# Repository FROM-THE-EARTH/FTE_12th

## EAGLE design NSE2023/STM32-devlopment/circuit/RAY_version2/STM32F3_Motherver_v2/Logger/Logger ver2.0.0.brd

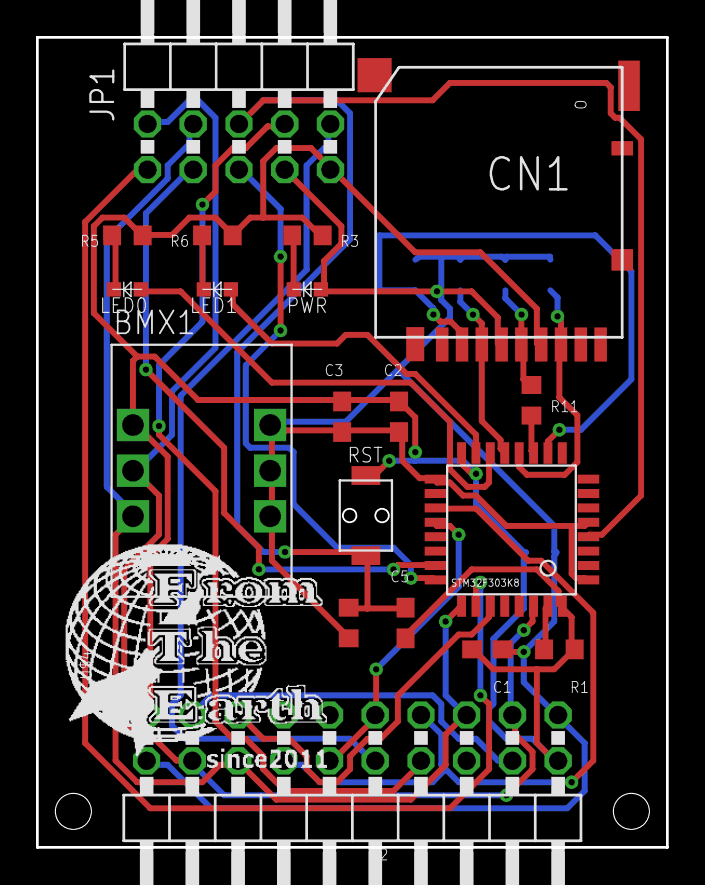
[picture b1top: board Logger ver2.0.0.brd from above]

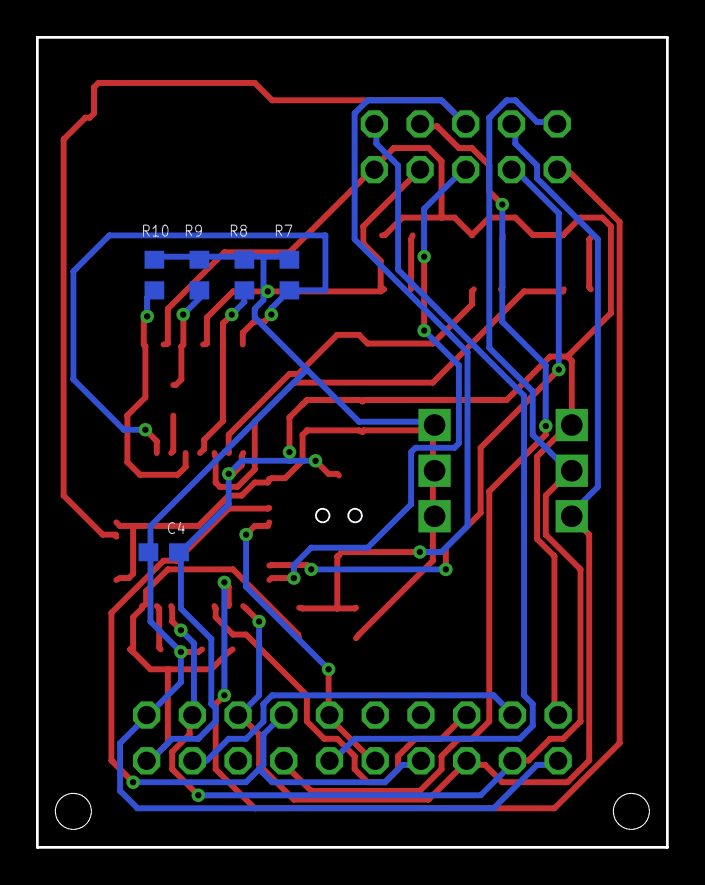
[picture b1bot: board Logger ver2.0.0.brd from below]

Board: 2 copper layers, 35.0 x 45.0 mm, 25 parts (5 on the bottom side), 25 nets.

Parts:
BMX1: BMX055
C1, C2: 100nF; C1608
C3: 4.7uF; C1608
C4: 10nF; C1608
C5: 0.1uF; C1608
CN1: DM3AT
JP1: 2X05/90
JP3: 2X10/90
LED0, LED1: OSXX1608C1A
PWR: OSXX1608C1A
R1, R7, R8, R9, R10: 10k; R0603
R2: 10k or DNF; R0603
R3, R5, R6, R11: 100; R0603
RST: TVAF06-A020B-R
U$1: STM32F303K8
U$4: F.T.E.LOGO; LOGO

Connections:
+3V3: BMX1.3V3, BMX1.VCC, BMX1.VCCIO, C1.1, C2.1, C3.1, C4.1, CN1.VDD, JP1.7, JP3.1, JP3.20, PWR.AN, R2.2, R7.2, R8.2, R9.2, R10.2, U$1.VDD, U$1.VDD2, U$1.VDDA
BOOT0: R1.1, U$1.BOOT
FPRAW: JP1.10, JP3.10
FP_CHECKER: JP3.15, U$1.PB4
GND: BMX1.GND, C1.2, C2.2, C3.2, C4.2, C5.2, CN1.VSS, JP1.9, JP3.2, JP3.19, R1.2, R3.1, R5.1, R6.1, RST.P$2, U$1.VSS, U$1.VSS2
LED0: LED0.AN, U$1.PB0
LED1: LED1.AN, U$1.PB1
LOGRX: JP3.7, JP3.14, U$1.PA9/UART1_TX
LOGTX: JP3.9, JP3.12, U$1.PA10/UART1_RX
MISO: CN1.DAT0, R10.1, U$1.PA6/SPI1_MISO
MOSI: CN1.CMD, R8.1, U$1.PA7/SPI1_MOSI
unnamed: PWR.CT, R3.2
unnamed: LED0.CT, R5.2
unnamed: LED1.CT, R6.2
unnamed: CN1.CLK, R9.1, R11.2
unnamed: JP3.4, JP3.17
NRST: C5.1, JP1.6, R2.1, RST.P$1, U$1.NRST
NSS: CN1.CD/DAT3, R7.1, U$1.PA4/SPI1_NSS
SCK: R11.1, U$1.PA5/SPI1_SCK
SCL: BMX1.SCL, JP1.4, JP3.5, JP3.16, U$1.PA15/I2C1_SCL
SDA: BMX1.SDA, JP1.2, JP3.3, JP3.18, U$1.PB7/I2C1_SDA
SW: JP1.8, JP3.8
SWCLK: JP1.5, U$1.PA14/SWCLK
SWDIO: JP1.3, U$1.PA13/SWDIO
SWO: JP1.1, U$1.PB3/SWO

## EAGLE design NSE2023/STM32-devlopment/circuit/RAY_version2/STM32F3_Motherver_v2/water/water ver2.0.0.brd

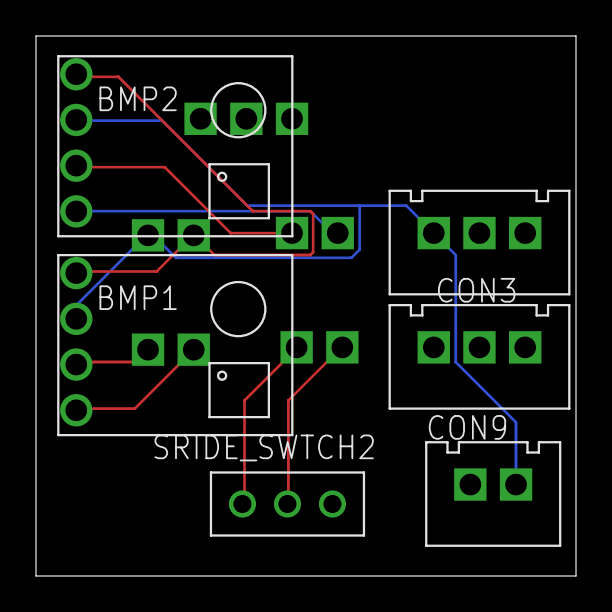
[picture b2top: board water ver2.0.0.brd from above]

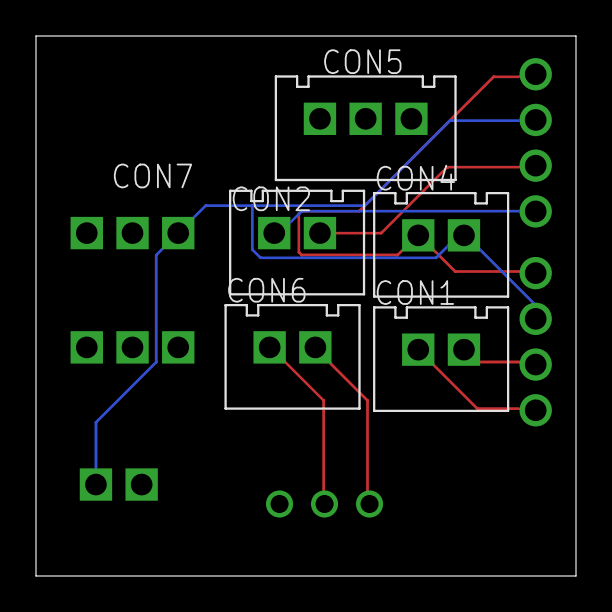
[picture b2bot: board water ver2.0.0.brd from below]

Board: 2 copper layers, 30.0 x 30.0 mm, 11 parts (5 on the bottom side), 8 nets.

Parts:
BMP1, BMP2: BMP180; GY-68
CON1, CON2, CON4, CON6, CON9: 2PIN
CON3, CON5, CON7: 3PIN
SRIDE_SWTCH2: SRIDE_SWITCH

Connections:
+3V3: BMP1.P1, BMP2.P1, CON4.P$1
GND: BMP1.P2, BMP2.P2, CON4.P$2, CON7.P$1, CON9.P$2
unnamed: CON6.P$2, SRIDE_SWTCH2.L
unnamed: CON6.P$1, SRIDE_SWTCH2.LR
SCL0: BMP1.P3, CON1.P$2
SCL1: BMP2.P3, CON2.P$2
SDA0: BMP1.P4, CON1.P$1
SDA1: BMP2.P4, CON2.P$1

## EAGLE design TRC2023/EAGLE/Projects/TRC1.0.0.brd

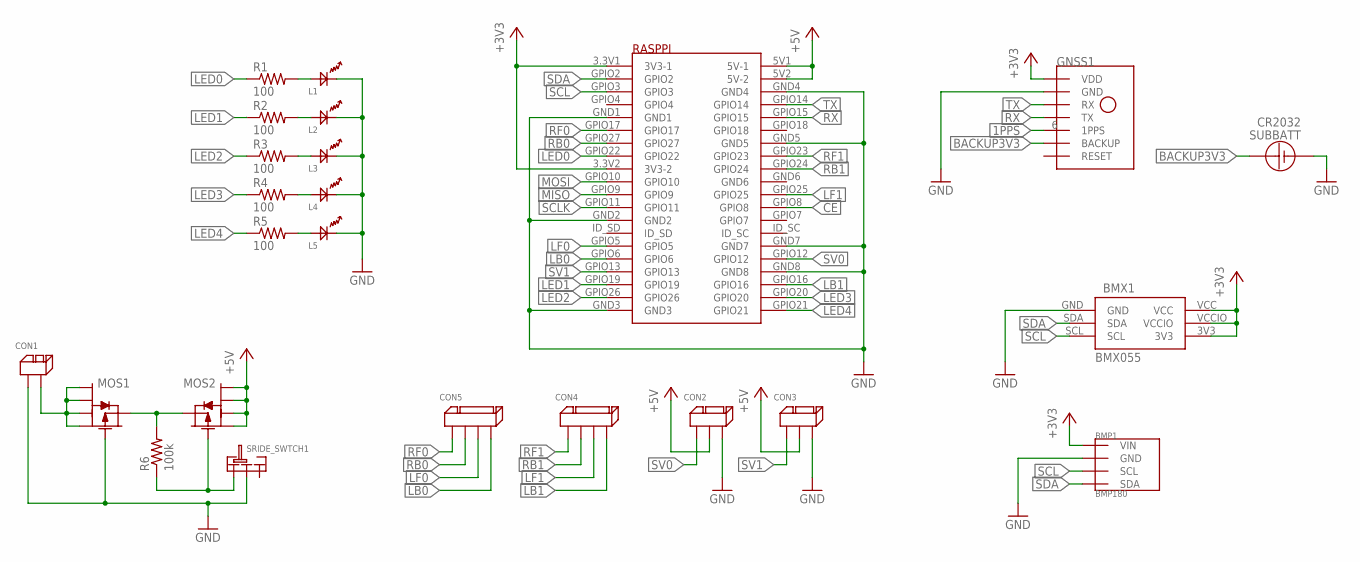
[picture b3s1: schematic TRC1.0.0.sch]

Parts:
BMP1: BMP180; GY-68
BMX1: BMX055
CON1: 2PIN
CON2, CON3: 3PIN
CON4, CON5: 4PIN
GNSS1: GYSFDMAXB
L1, L2, L3, L4, L5: OSXX1608C1A
MOS1, MOS2: PCH_SSM6J808R; SSM6J808R
R1, R2, R3, R4, R5: 100; R0201
R6: 100k; R0201
RASPPI: RASPBERYPIZEROW
SRIDE_SWTCH1: SRIDE_SWITCH
SUBBATT: CR2032

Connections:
1PPS: GNSS1.6 (1PPS)
+3V3: BMP1.P1 (VIN), BMX1.3V3, BMX1.VCC, BMX1.VCCIO, GNSS1.16 (VDD), RASPPI.3.3V1 (3V3-1), RASPPI.3.3V2 (3V3-2)
+5V: CON2.P$2, CON3.P$2, MOS2.1, MOS2.2, MOS2.5, MOS2.6, RASPPI.5V1 (5V-1), RASPPI.5V2 (5V-2)
BACKUP3V3: GNSS1.14 (BACKUP), SUBBATT.VCC, SUBBATT.VCC2 (VCC)
CE: RASPPI.GPIO8
GND: BMP1.P2 (GND), BMX1.GND, CON1.P$1, CON2.P$3, CON3.P$3, GNSS1.1 (GND), GNSS1.2 (GND), GNSS1.7 (GND), GNSS1.10 (GND), GNSS1.12 (GND), GNSS1.19 (GND), GNSS1.20 (GND), L1.CT, L2.CT, L3.CT, L4.CT, L5.CT, MOS1.3, RASPPI.GND1, RASPPI.GND2, RASPPI.GND3, RASPPI.GND4, RASPPI.GND5, RASPPI.GND7, RASPPI.GND8, SRIDE_SWTCH1.LR, SUBBATT.GND
LB0: CON5.P$4, RASPPI.GPIO6
LB1: CON4.P$4, RASPPI.GPIO16
LED0: R1.1, RASPPI.GPIO22
LED1: R2.1, RASPPI.GPIO19
LED2: R3.1, RASPPI.GPIO26
LED3: R4.1, RASPPI.GPIO20
LED4: R5.1, RASPPI.GPIO21
LF0: CON5.P$3, RASPPI.GPIO5
LF1: CON4.P$3, RASPPI.GPIO25
MISO: RASPPI.GPIO9
MOSI: RASPPI.GPIO10
unnamed: L1.AN, R1.2
unnamed: L2.AN, R2.2
unnamed: L3.AN, R3.2
unnamed: L4.AN, R4.2
unnamed: L5.AN, R5.2
unnamed: MOS1.4, MOS2.4, R6.2
unnamed: MOS2.3, R6.1, SRIDE_SWTCH1.L
unnamed: CON1.P$2, MOS1.1, MOS1.2, MOS1.5, MOS1.6
RB0: CON5.P$2, RASPPI.GPIO27
RB1: CON4.P$2, RASPPI.GPIO24
RF0: CON5.P$1, RASPPI.GPIO17
RF1: CON4.P$1, RASPPI.GPIO23
RX: GNSS1.5 (TX), RASPPI.GPIO15
SCL: BMP1.P3 (SCL), BMX1.SCL, RASPPI.GPIO3
SCLK: RASPPI.GPIO11
SDA: BMP1.P4 (SDA), BMX1.SDA, RASPPI.GPIO2
SV0: CON2.P$1, RASPPI.GPIO12
SV1: CON3.P$1, RASPPI.GPIO13
TX: GNSS1.3 (RX), RASPPI.GPIO14

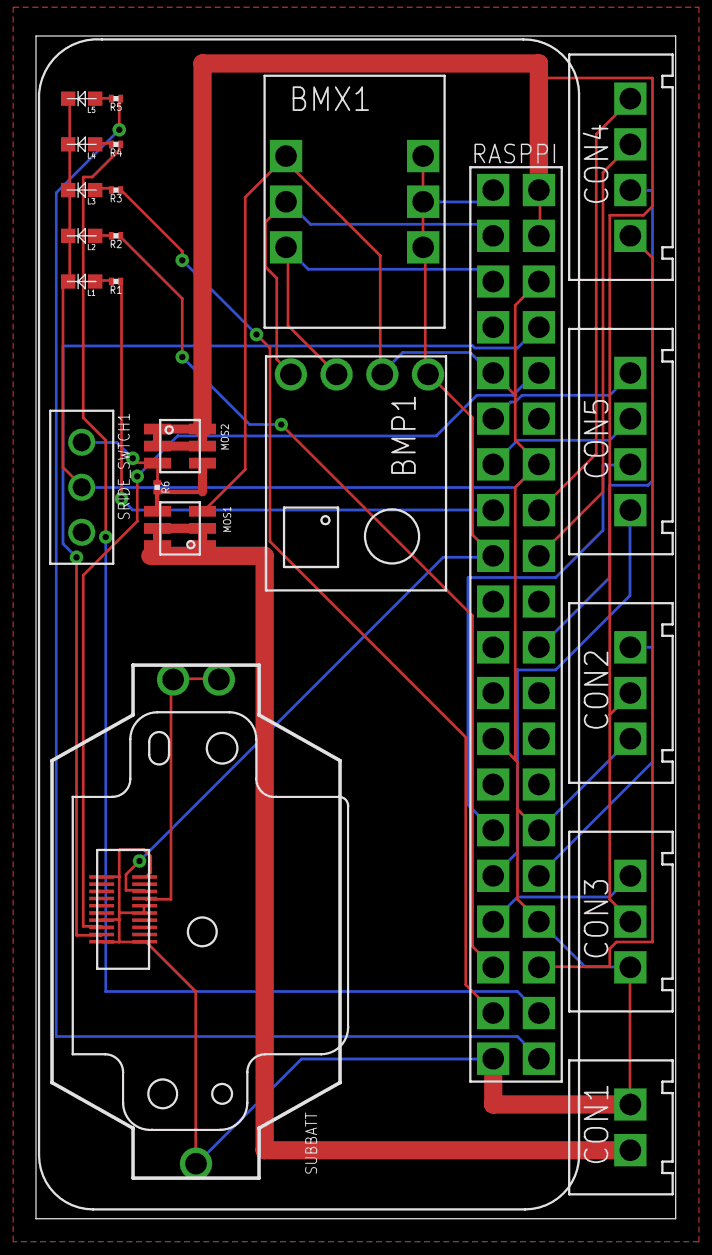
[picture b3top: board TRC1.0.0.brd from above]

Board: 2 copper layers, 35.5 x 65.7 mm, 24 parts (0 on the bottom side), 31 nets.

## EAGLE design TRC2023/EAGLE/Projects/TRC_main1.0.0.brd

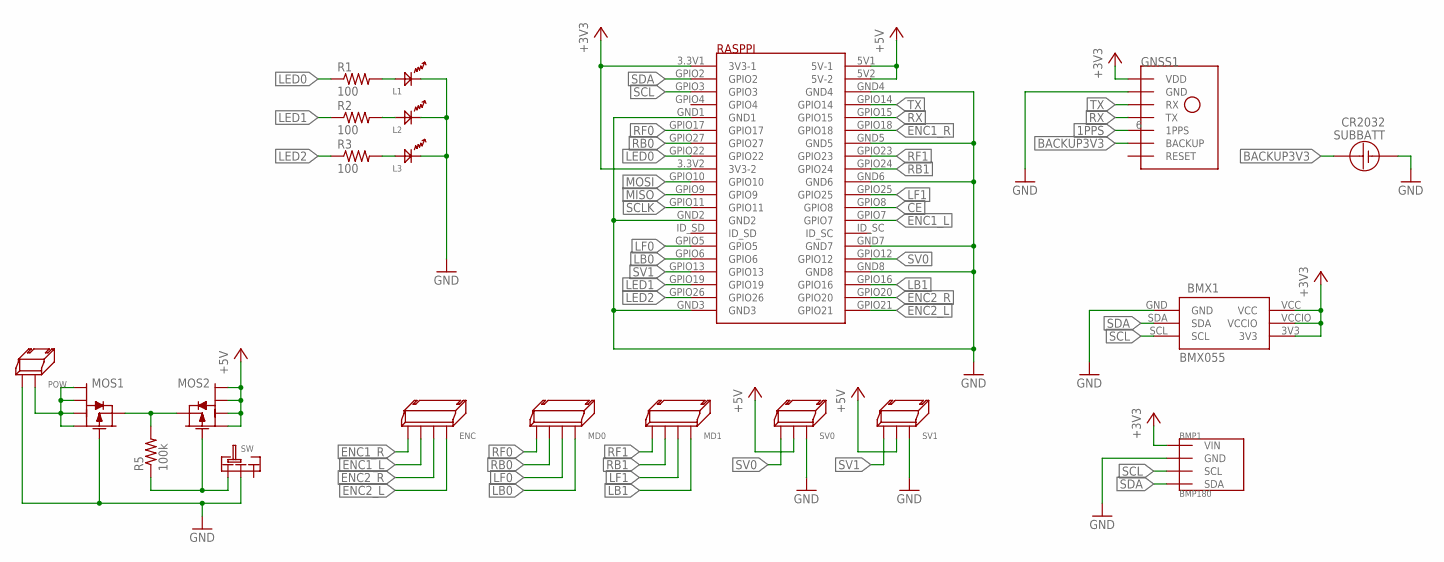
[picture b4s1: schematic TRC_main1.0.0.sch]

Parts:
BMP1: BMP180; GY-68
BMX1: BMX055
ENC: 4PIN_SIDE
GNSS1: GYSFDMAXB
L1, L2, L3: OSXX1608C1A
MD0, MD1: 4PIN_SIDE
MOS1, MOS2: PCH_SSM6J808R; SSM6J808R
POW: 2PIN_SIDE
R1, R2, R3: 100; R0603
R5: 100k; R0603
RASPPI: RASPBERYPIZEROW
SUBBATT: CR2032
SV0, SV1: 3PIN_SIDE
SW: SRIDE_SWITCH

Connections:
1PPS: GNSS1.6 (1PPS)
+3V3: BMP1.P1 (VIN), BMX1.3V3, BMX1.VCC, BMX1.VCCIO, GNSS1.16 (VDD), RASPPI.3.3V1 (3V3-1), RASPPI.3.3V2 (3V3-2)
+5V: MOS2.1, MOS2.2, MOS2.5, MOS2.6, RASPPI.5V1 (5V-1), RASPPI.5V2 (5V-2), SV0.P$1, SV1.P$1
BACKUP3V3: GNSS1.14 (BACKUP), SUBBATT.VCC, SUBBATT.VCC2 (VCC)
CE: RASPPI.GPIO8
ENC1_L: ENC.P$1, RASPPI.GPIO7
ENC1_R: ENC.P$2, RASPPI.GPIO18
ENC2_L: ENC.P$4, RASPPI.GPIO21
ENC2_R: ENC.P$3, RASPPI.GPIO20
GND: BMP1.P2 (GND), BMX1.GND, GNSS1.1 (GND), GNSS1.2 (GND), GNSS1.7 (GND), GNSS1.10 (GND), GNSS1.12 (GND), GNSS1.19 (GND), GNSS1.20 (GND), L1.CT, L2.CT, L3.CT, MOS1.3, POW.P$2, RASPPI.GND1, RASPPI.GND2, RASPPI.GND3, RASPPI.GND4, RASPPI.GND5, RASPPI.GND6, RASPPI.GND7, RASPPI.GND8, SUBBATT.GND, SV0.P$3, SV1.P$3, SW.LR
LB0: MD0.P$4, RASPPI.GPIO6
LB1: MD1.P$4, RASPPI.GPIO16
LED0: R1.1, RASPPI.GPIO22
LED1: R2.1, RASPPI.GPIO19
LED2: R3.1, RASPPI.GPIO26
LF0: MD0.P$3, RASPPI.GPIO5
LF1: MD1.P$3, RASPPI.GPIO25
MISO: RASPPI.GPIO9
MOSI: RASPPI.GPIO10
unnamed: L1.AN, R1.2
unnamed: L2.AN, R2.2
unnamed: L3.AN, R3.2
unnamed: MOS1.4, MOS2.4, R5.2
unnamed: MOS2.3, R5.1, SW.L
unnamed: MOS1.1, MOS1.2, MOS1.5, MOS1.6, POW.P$1
RB0: MD0.P$1, RASPPI.GPIO27
RB1: MD1.P$1, RASPPI.GPIO24
RF0: MD0.P$2, RASPPI.GPIO17
RF1: MD1.P$2, RASPPI.GPIO23
RX: GNSS1.5 (TX), RASPPI.GPIO15
SCL: BMP1.P3 (SCL), BMX1.SCL, RASPPI.GPIO3
SCLK: RASPPI.GPIO11
SDA: BMP1.P4 (SDA), BMX1.SDA, RASPPI.GPIO2
SV0: RASPPI.GPIO12, SV0.P$2
SV1: RASPPI.GPIO13, SV1.P$2
TX: GNSS1.3 (RX), RASPPI.GPIO14

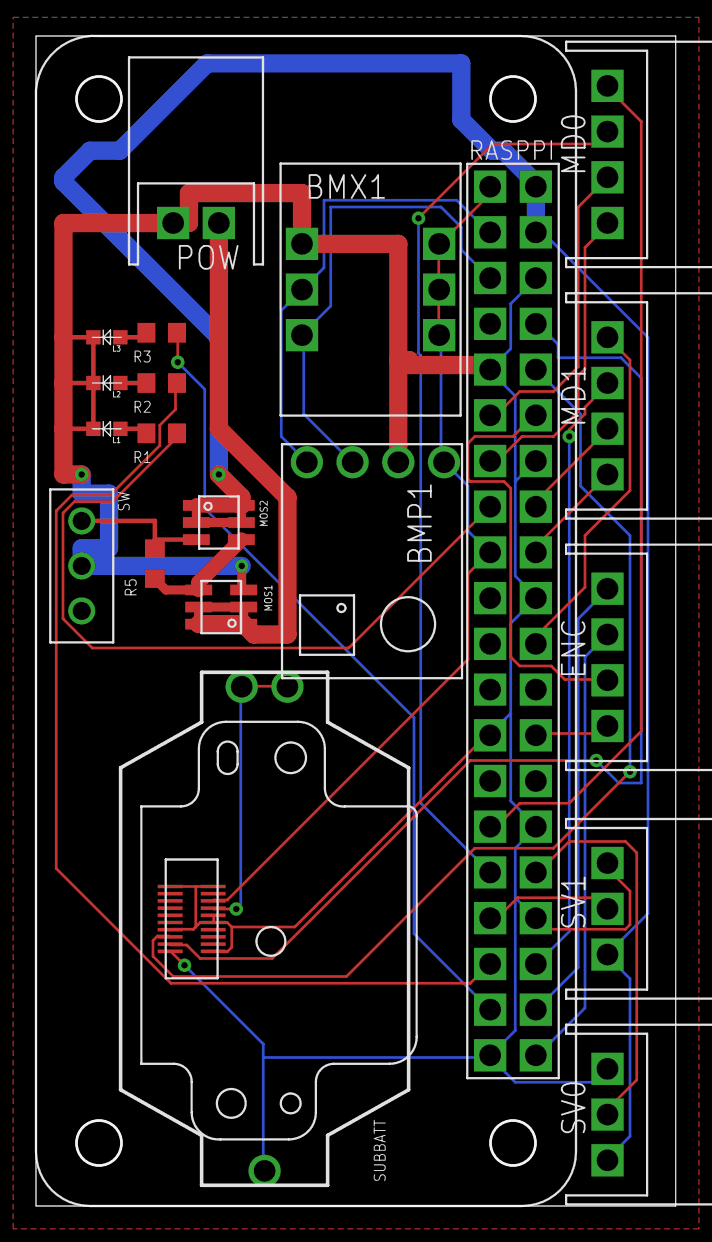
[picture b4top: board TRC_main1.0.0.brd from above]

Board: 2 copper layers, 35.5 x 65.0 mm, 21 parts (0 on the bottom side), 31 nets.
